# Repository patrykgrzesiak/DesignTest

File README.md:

# DesignTest
Test Repo for KiCad demo

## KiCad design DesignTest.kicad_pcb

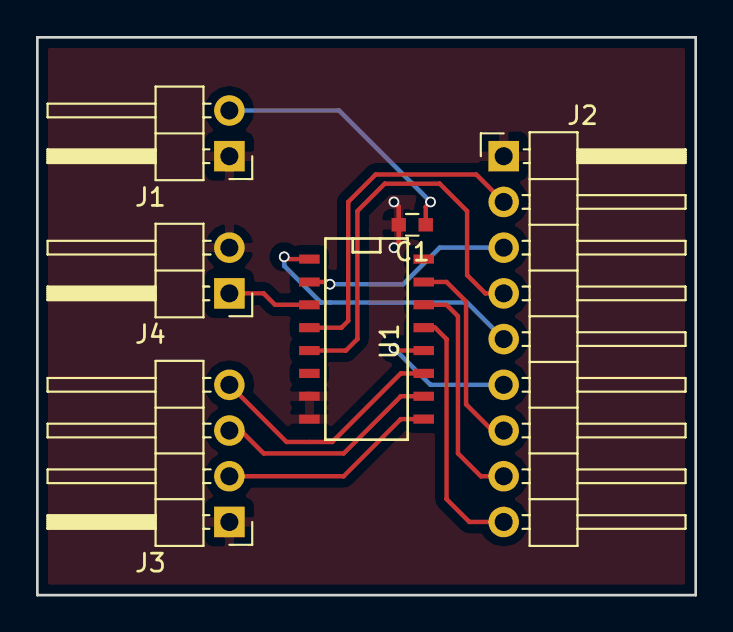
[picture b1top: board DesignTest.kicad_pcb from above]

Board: 2 copper layers, 36.6 x 31.0 mm, 6 parts (0 on the bottom side), 14 nets.

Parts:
C1: C; C_0603
J1, J4: Conn_01x02; Pin_Header_Angled_1x02_Pitch2.54mm
J2: Conn_01x09; Pin_Header_Angled_1x09_Pitch2.54mm
J3: Conn_01x04; Pin_Header_Angled_1x04_Pitch2.54mm
U1: 4051; SO-16-N

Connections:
GND: C1.2, J1.1, J2.1, J3.1, J4.2, U1.7, U1.8
unnamed: J2.2, U1.4
unnamed: J2.3, U1.2
unnamed: J2.4, U1.5
unnamed: J2.5, U1.1
unnamed: J2.6, U1.12
unnamed: J2.7, U1.15
unnamed: J2.8, U1.14
unnamed: J2.9, U1.13
unnamed: J3.2, U1.9
unnamed: J3.3, U1.10
unnamed: J3.4, U1.11
unnamed: J4.1, U1.3
VDD: C1.1, J1.2, U1.16

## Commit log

2018-02-05 Fist commit
2018-02-05 development - added text to PCB
2018-02-05 Ready to go
